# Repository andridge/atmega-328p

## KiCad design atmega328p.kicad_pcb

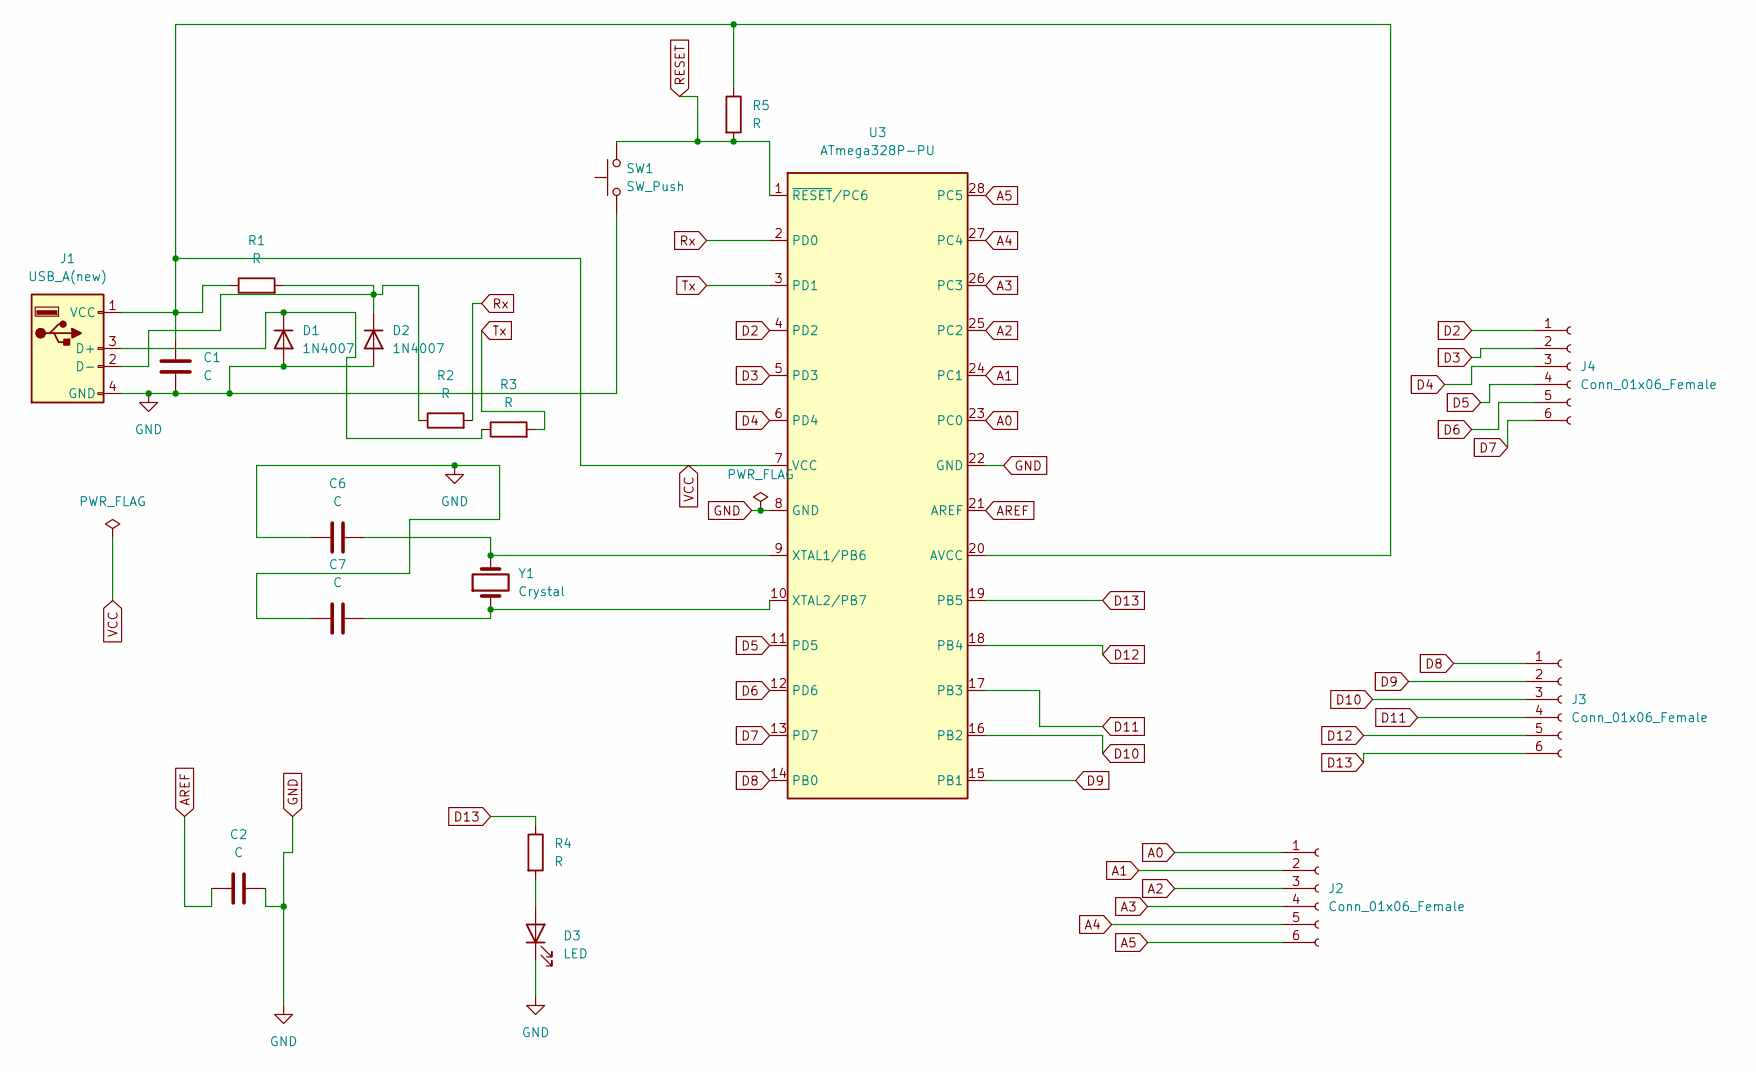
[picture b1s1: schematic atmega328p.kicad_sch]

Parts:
C1: C; CP_Radial_D13.0mm_P5.00mm
C2, C6, C7: C; C_Disc_D3.0mm_W1.6mm_P2.50mm
D1, D2: 1N4007; D_DO-41_SOD81_P10.16mm_Horizontal
D3: LED; LED_D3.0mm_Clear
J1: USB_A(new); USB_A_Molex_67643_Horizontal
J2, J3, J4: Conn_01x06_Female; PinSocket_1x06_P2.54mm_Vertical
R1, R2, R3: R; R_Axial_DIN0411_L9.9mm_D3.6mm_P12.70mm_Horizontal
R4, R5: R; R_LDR_5.2x5.2mm_P3.5mm_Horizontal
SW1: SW_Push; SW_PUSH_6mm
U3: ATmega328P-PU; DIP-28_W7.62mm
Y1: Crystal; Crystal_HC49-4H_Vertical

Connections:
A0: J2.1, U3.23 (PC0)
A1: J2.2, U3.24 (PC1)
A2: J2.3, U3.25 (PC2)
A3: J2.4, U3.26 (PC3)
A4: J2.5, U3.27 (PC4)
A5: J2.6, U3.28 (PC5)
AREF: C2.1, U3.21 (AREF)
D2: J4.1, U3.4 (PD2)
D3: J4.2, U3.5 (PD3)
D4: J4.3, U3.6 (PD4)
D5: J4.4, U3.11 (PD5)
D6: J4.5, U3.12 (PD6)
D7: J4.6, U3.13 (PD7)
D8: J3.1, U3.14 (PB0)
D9: J3.2, U3.15 (PB1)
D10: J3.3, U3.16 (PB2)
D11: J3.4, U3.17 (PB3)
D12: J3.5, U3.18 (PB4)
D13: J3.6, R4.1, U3.19 (PB5)
GND: C1.2, C2.2, C6.1, C7.1, D1.2 (A), D2.2 (A), D3.1 (K), J1.4 (GND), SW1.1, U3.8 (GND), U3.22 (GND)
unnamed: C6.2, U3.9 (XTAL1/PB6), Y1.2
unnamed: C7.2, U3.10 (XTAL2/PB7), Y1.1
unnamed: D1.1 (K), J1.3 (D+), R3.1
unnamed: D3.2 (A), R4.2
unnamed: D2.1 (K), J1.2 (D-), R1.2, R2.1
RESET: R5.2, SW1.2, U3.1 (~RESET/PC6)
Rx: R2.2, U3.2 (PD0)
Tx: R3.2, U3.3 (PD1)
VCC: C1.1, J1.1 (VCC), R1.1, R5.1, U3.7 (VCC), U3.20 (AVCC)

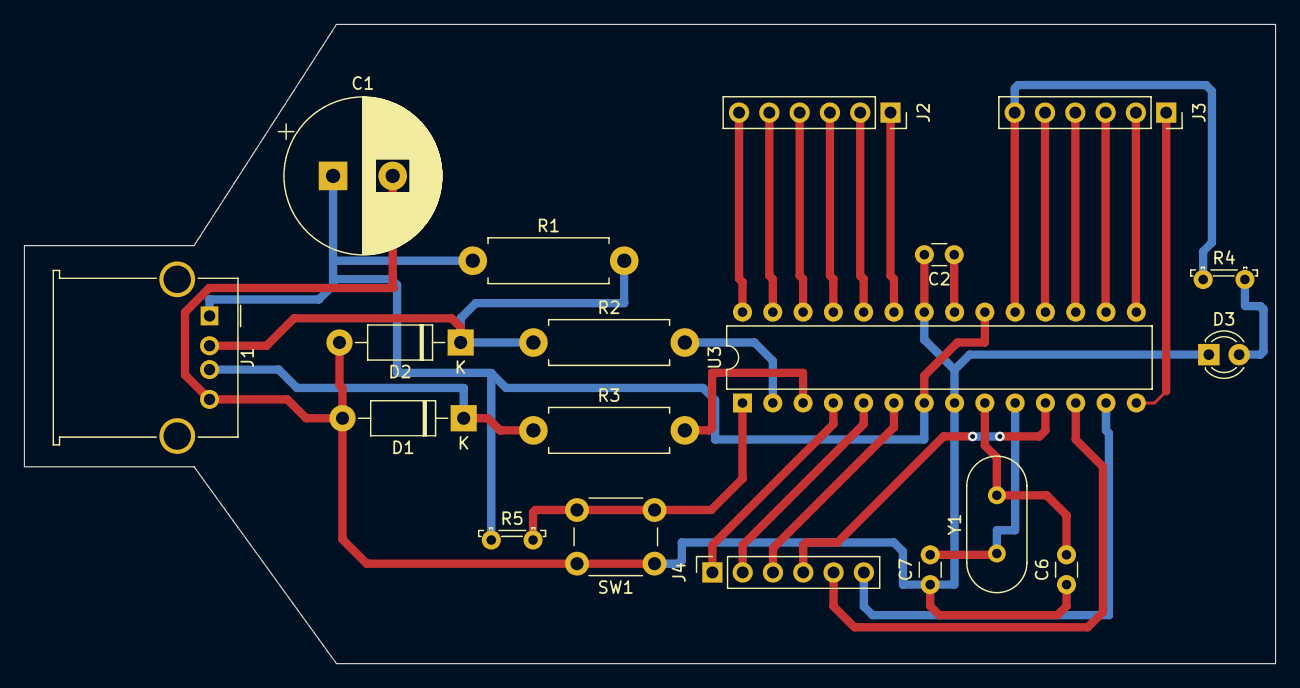
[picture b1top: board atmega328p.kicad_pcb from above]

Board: 2 copper layers, 104.9 x 53.6 mm, 19 parts (0 on the bottom side), 29 nets.
